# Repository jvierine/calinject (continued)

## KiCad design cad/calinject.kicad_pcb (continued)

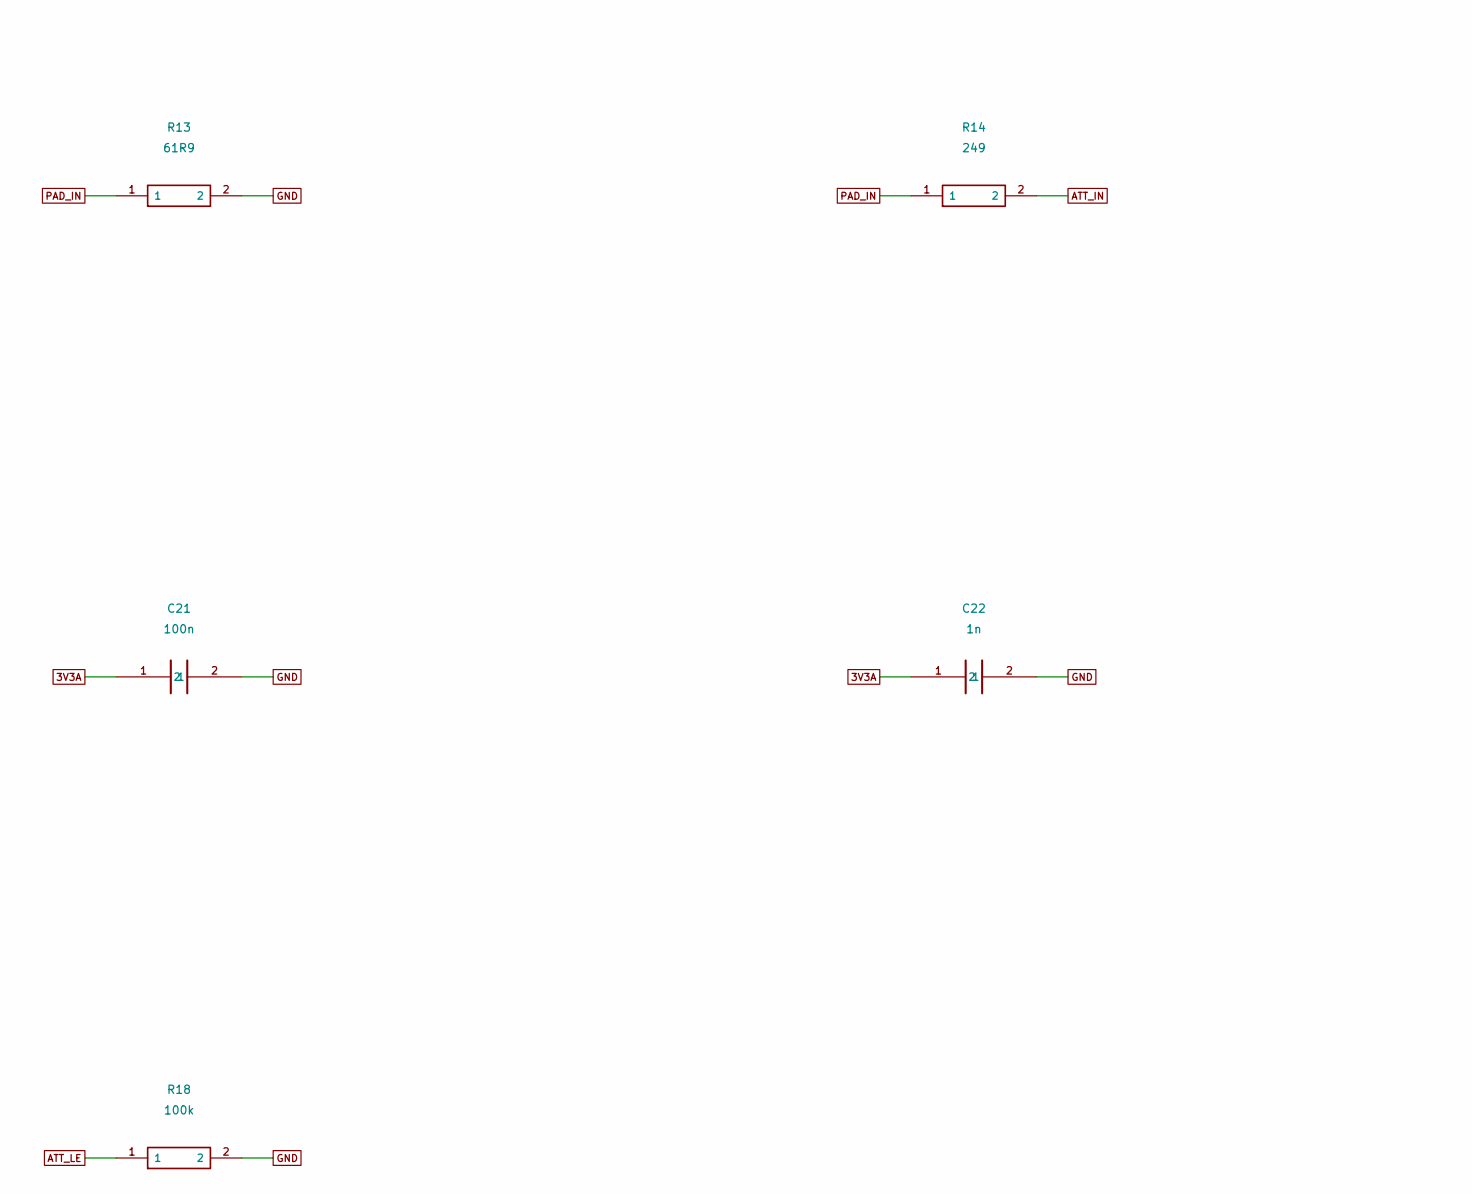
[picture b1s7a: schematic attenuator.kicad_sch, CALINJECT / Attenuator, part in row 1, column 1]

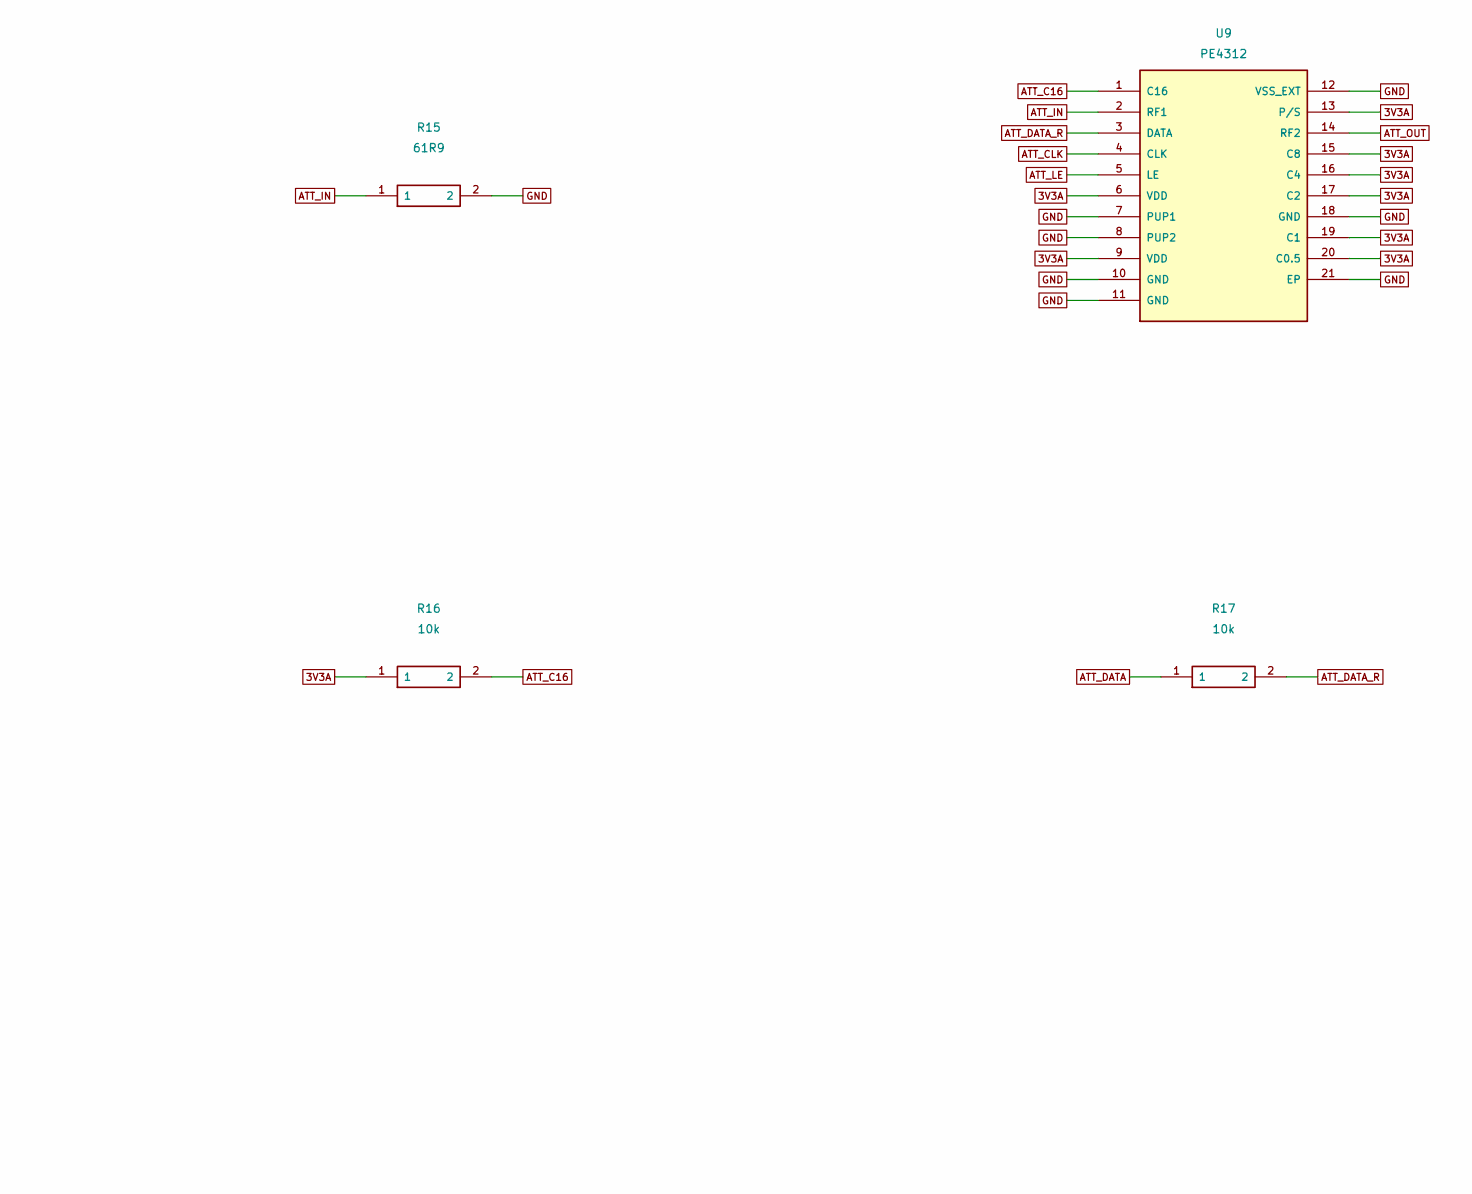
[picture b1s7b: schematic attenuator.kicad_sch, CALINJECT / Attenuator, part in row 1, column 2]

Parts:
C21: 100n; C_0603_C21
C22: 1n; C_0603_C22
R13: 61R9; R_0603_R13
R14: 249; R_0603_R14
R15: 61R9; R_0603_R15
R16: 10k; R_0603_R16
R17: 10k; R_0603_R17
R18: 100k; R_0603_R18
U9: PE4312; QFN20_4x4_EP_U9

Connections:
3V3A: C21.1, C22.1, R16.1, U9.6 (VDD), U9.9 (VDD), U9.13 (P/S), U9.15 (C8), U9.16 (C4), U9.17 (C2), U9.19 (C1), U9.20 (C0.5); also elsewhere on the board
ATT_C16: R16.2, U9.1 (C16)
ATT_CLK: U9.4 (CLK); also elsewhere on the board
ATT_DATA: R17.1; also elsewhere on the board
ATT_DATA_R: R17.2, U9.3 (DATA)
ATT_IN: R14.2, R15.1, U9.2 (RF1)
ATT_LE: R18.1, U9.5 (LE); also elsewhere on the board
ATT_OUT: U9.14 (RF2); also elsewhere on the board
GND: C21.2, C22.2, R13.2, R15.2, R18.2, U9.7 (PUP1), U9.8 (PUP2), U9.10 (GND), U9.11 (GND), U9.12 (VSS_EXT), U9.18 (GND), U9.21 (EP); also elsewhere on the board
PAD_IN: R13.1, R14.1; also elsewhere on the board

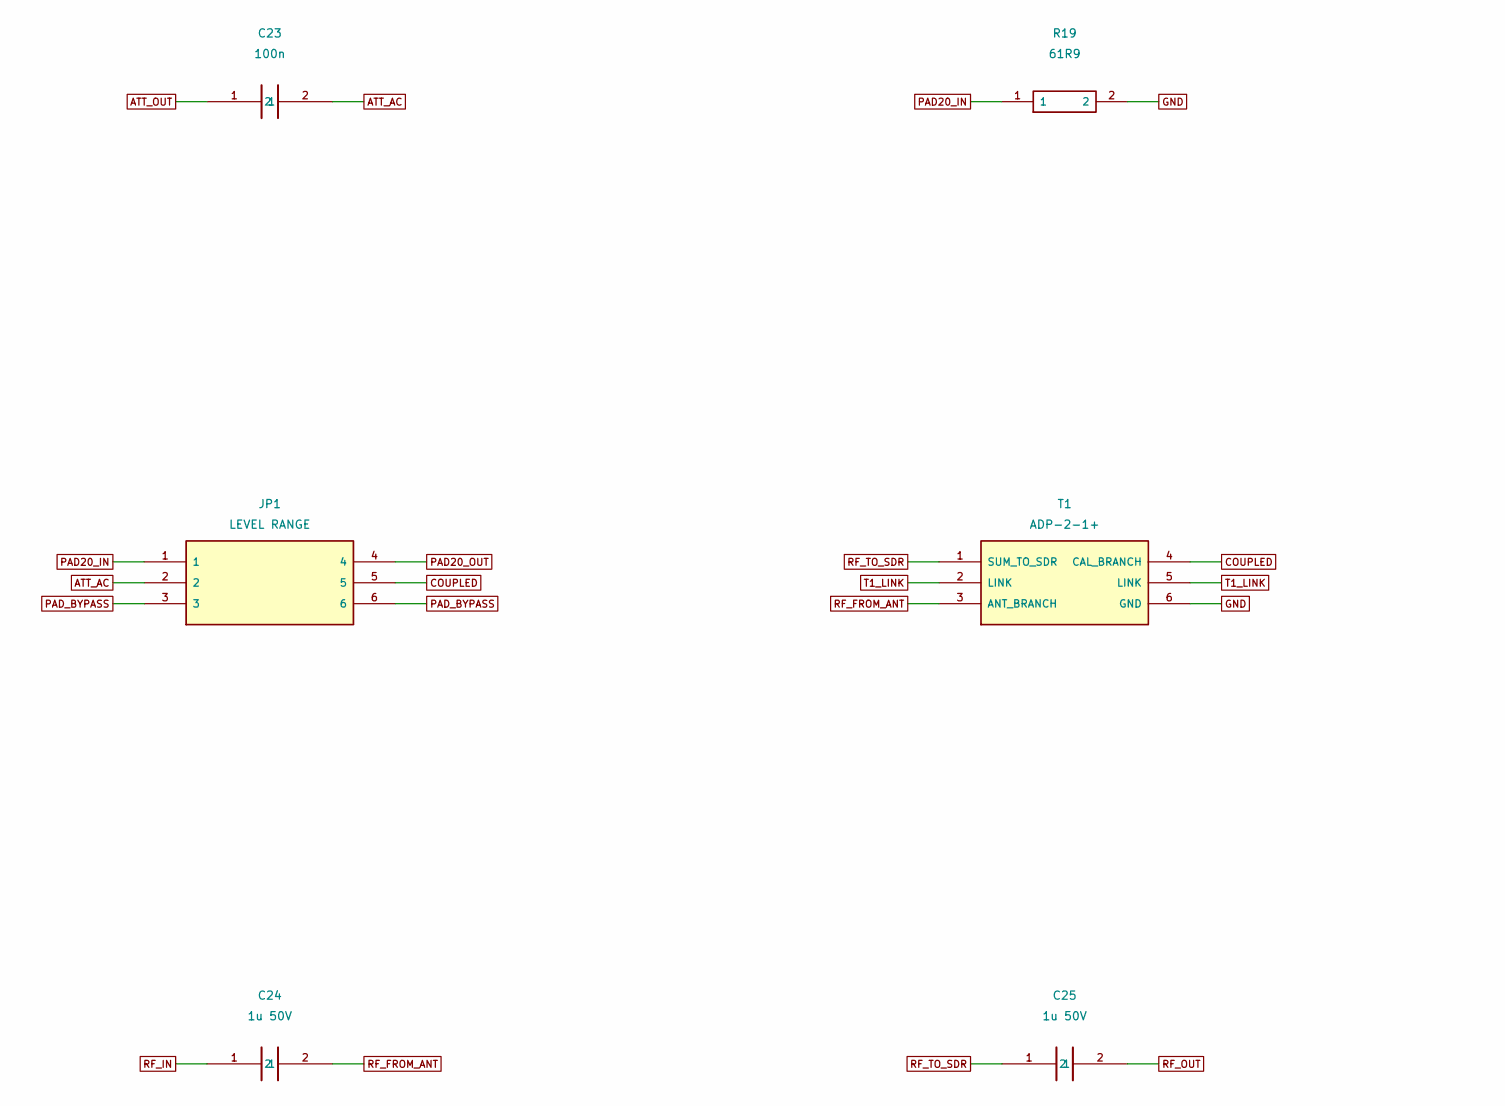
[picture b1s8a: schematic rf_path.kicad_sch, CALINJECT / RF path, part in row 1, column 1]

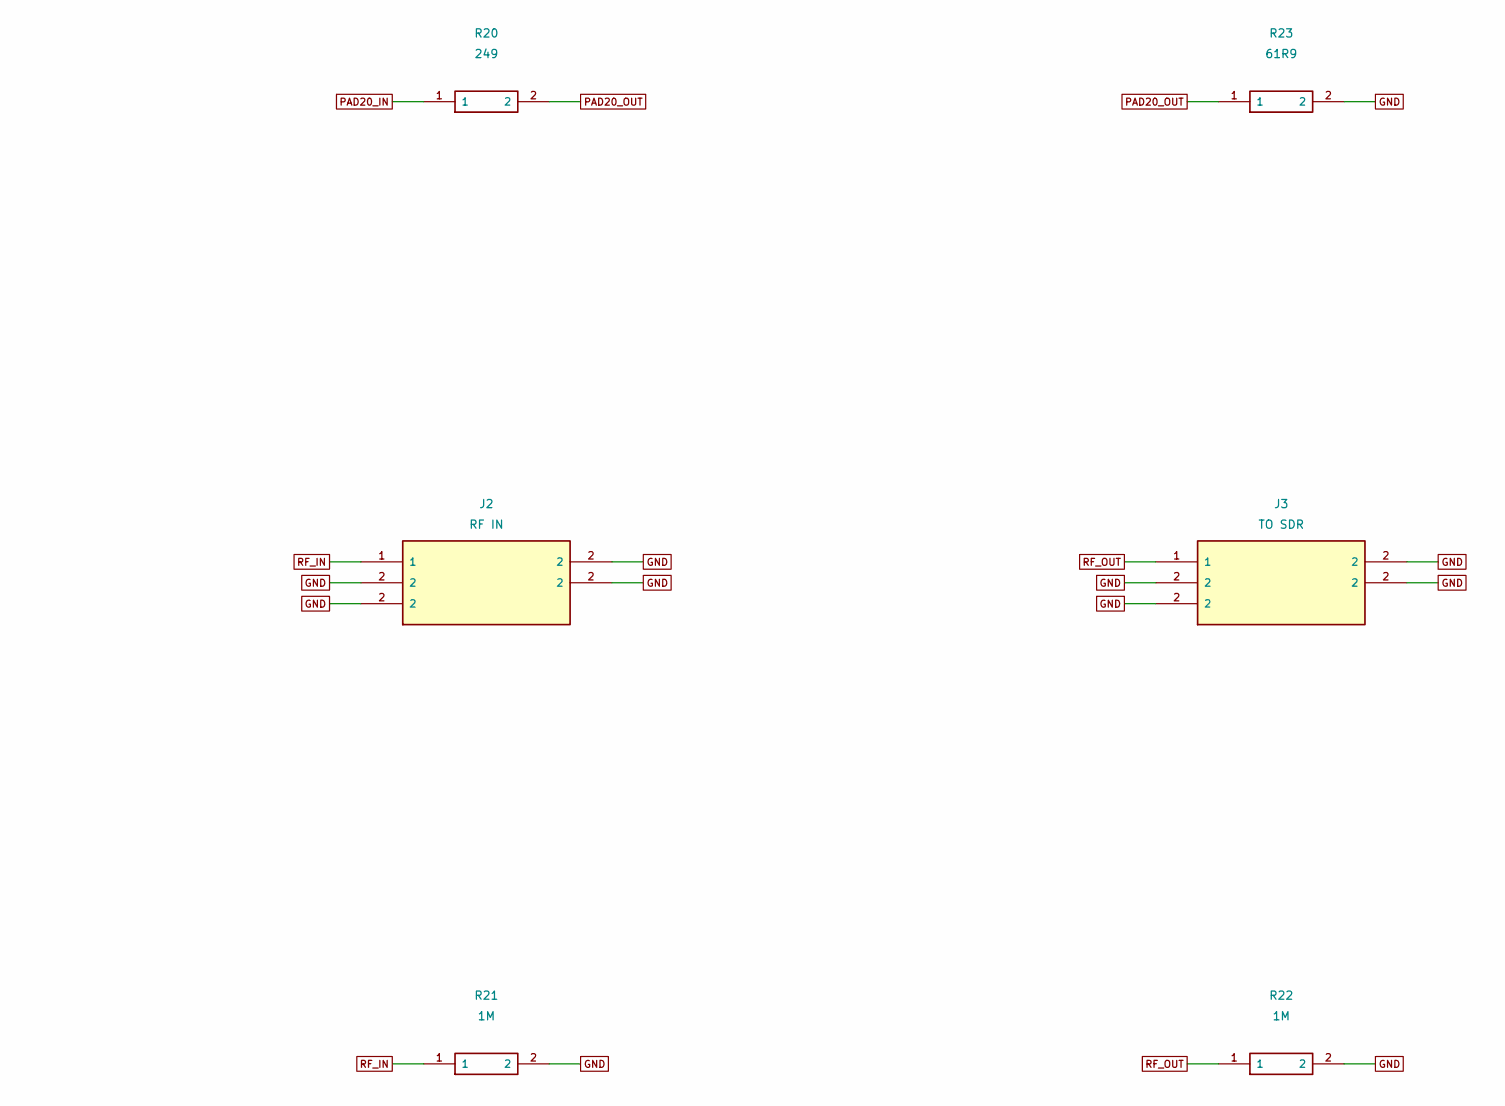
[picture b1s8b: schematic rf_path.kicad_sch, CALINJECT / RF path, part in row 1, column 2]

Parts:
C23: 100n; C_0603_C23
C24: 1u 50V; C_0805_C24
C25: 1u 50V; C_0805_C25
J2: RF IN; SMA_KWE_RA_J2
J3: TO SDR; SMA_KWE_RA_J3
JP1: LEVEL RANGE; Range_2x3_JP1
R19: 61R9; R_0603_R19
R20: 249; R_0603_R20
R21: 1M; R_0603_R21
R22: 1M; R_0603_R22
R23: 61R9; R_0603_R23
T1: ADP-2-1+; MiniCircuits_CD636_T1

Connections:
ATT_AC: C23.2, JP1.2
ATT_OUT: C23.1; also elsewhere on the board
COUPLED: JP1.5, T1.4 (CAL_BRANCH)
GND: J2.2, J3.2, R19.2, R21.2, R22.2, R23.2, T1.6 (GND); also elsewhere on the board
PAD20_IN: JP1.1, R19.1, R20.1
PAD20_OUT: JP1.4, R20.2, R23.1
PAD_BYPASS: JP1.3, JP1.6
RF_FROM_ANT: C24.2, T1.3 (ANT_BRANCH)
RF_IN: C24.1, J2.1, R21.1
RF_OUT: C25.2, J3.1, R22.1
RF_TO_SDR: C25.1, T1.1 (SUM_TO_SDR)
T1_LINK: T1.2 (LINK), T1.5 (LINK)

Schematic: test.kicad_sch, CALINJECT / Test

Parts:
TP1: PPS; TestPoint_TP1
TP2: 10M; TestPoint_TP2
TP3: GATE; TestPoint_TP3
TP4: VC; TestPoint_TP4
TP5: GND; TestPoint_TP5
TP6: 3V3; TestPoint_TP6

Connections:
3V3A: TP6.1; also elsewhere on the board
BURST_GATE: TP3.1; also elsewhere on the board
GND: TP5.1; also elsewhere on the board
PPS: TP1.1; also elsewhere on the board
TCXO_COUNT: TP2.1; also elsewhere on the board
VCTRL: TP4.1; also elsewhere on the board

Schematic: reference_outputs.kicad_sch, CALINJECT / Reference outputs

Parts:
C27: 100n; C_0603_C27
C28: 100n; C_0603_C28
J4: 10 MHz OUT; SMA_KWE_RA_J4
J5: 1 PPS OUT; SMA_KWE_RA_J5
R24: 100; R_0603_R24
R25: 100; R_0603_R25
R26: 0; R_0603_R26
R27: 10k; R_0603_R27
R28: 100; R_0603_R28
R29: 100; R_0603_R29
R30: 0; R_0603_R30
R31: 10k; R_0603_R31
R32: 1M; R_0603_R32
R33: 1M; R_0603_R33
U10: SN74LVC2G125; SSOP8_DCT_U10
U11: SN74LVC2G125; SSOP8_DCT_U11

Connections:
3V3A: C27.1, C28.1, R27.2, R31.2, U10.8 (VCC), U11.8 (VCC); also elsewhere on the board
CLK10: U10.2 (1A), U10.5 (2A); also elsewhere on the board
GND: C27.2, C28.2, J4.2, J5.2, R32.2, R33.2, U10.4 (GND), U11.4 (GND); also elsewhere on the board
PPS: U11.2 (1A), U11.5 (2A); also elsewhere on the board
REF10_OE_N: R27.1, U10.1 (1OE_N), U10.7 (2OE_N); also elsewhere on the board
REF10_OUT: J4.1, R26.2, R32.1
REF10_SUM: R24.2, R25.2, R26.1
REFPPS_OE_N: R31.1, U11.1 (1OE_N), U11.7 (2OE_N); also elsewhere on the board
REFPPS_OUT: J5.1, R30.2, R33.1
REFPPS_SUM: R28.2, R29.2, R30.1
U10_A: R24.1, U10.6 (1Y)
U10_B: R25.1, U10.3 (2Y)
U11_A: R28.1, U11.6 (1Y)
U11_B: R29.1, U11.3 (2Y)

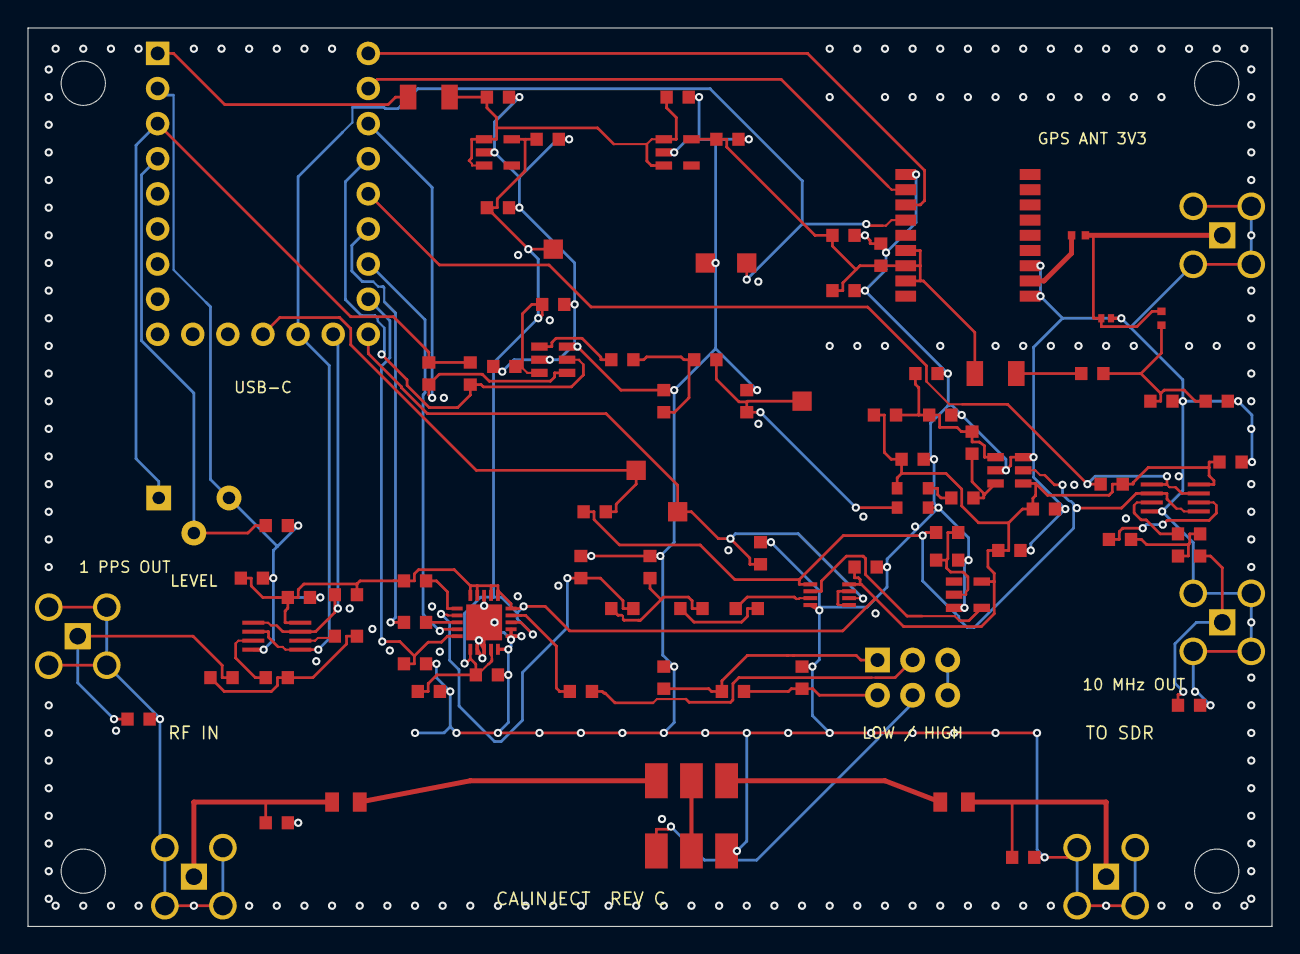
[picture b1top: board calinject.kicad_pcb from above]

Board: 4 copper layers, 90.0 x 65.0 mm, 99 parts (0 on the bottom side), 58 nets.

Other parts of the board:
H1: M3; Mount_M3_H1
H2: M3; Mount_M3_H2
H3: M3; Mount_M3_H3
H4: M3; Mount_M3_H4

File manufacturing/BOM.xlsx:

Designator | Comment | Footprint | Manufacturer | Manufacturer Part | Quantity | Assembly | LCSC Part #
U1 | RP2040-Zero | RP2040_Zero | Waveshare | RP2040-Zero | 1 | FACTORY MODULE | C5350143
U2,U3 | AP2112K-3.3 | SOT23_5 | Diodes Incorporated | AP2112K-3.3TRG1 | 2 | SMT
F1 | 500mA | F_1206 | Littelfuse | 1206L050/15YR | 1 | SMT
C1,C2,C3,C4,C6,C11,C12 | 4u7 | C_0603 | Murata | GRM188R61A475KE15D | 7 | SMT
U4 | MAX-M10S | MAX_M10S | u-blox | MAX-M10S-00B | 1 | SMT | C4153167
C5,C8,C10,C13,C15,C16,C18,C19,C21,C26,C27,C28,C29,C31,C32,C33 | 100n | C_0603 | Murata | GRM188R71C104KA01D | 16 | SMT
J1 | GPS ANT | SMA_KWE_RA | Lian Xin Technology | SMA-KWE | 1 | THT | C7498154
C7 | 100p | C_0402 | Murata | GRM1555C1H101JA01D | 1 | SMT
L1 | 27n | L_0402 | Murata | LQW15AN27NG80D | 1 | SMT
F2 | 50mA | F_1206 | Littelfuse | 1206L005/60WR | 1 | SMT
R1,R26,R30 | 0 | R_0603 | Yageo | RC0603FR-070RL | 3 | SMT
C9,C14,C22 | 1n | C_0603 | Murata | GRM1885C1H102JA01D | 3 | SMT
D1 | PESD5V0F1BL | DFN1006_2 | Nexperia | PESD5V0F1BL,315 | 1 | SMT | C45961
U5 | MCP4725A1 | SOT23_6 | Microchip | MCP4725A1T-E/CH | 1 | SMT | C61423
R2,R3 | 4k7 | R_0603 | Yageo | RC0603FR-074K7L | 2 | SMT
R4,R5 | 1k | R_0603 | Yageo | RC0603FR-071KL | 2 | SMT
Y1 | 10MHz VCTCXO | KDS_DSA321SDN | KDS Daishinku | 1XTV10000MDA | 1 | SMT | C253701
R6,R7,R8,R16,R17,R27,R31 | 10k | R_0603 | Yageo | RC0603FR-0710KL | 7 | SMT
U6 | TLV3501 | SOT23_6 | Texas Instruments | TLV3501AIDBVR | 1 | SMT
R9 | 330 | R_0603 | Yageo | RC0603FR-07330RL | 1 | SMT
R10 | 220 | R_0603 | Yageo | RC0603FR-07220RL | 1 | SMT
C17 | 22p | C_0603 | Samsung Electro-Mechanics | CL10C220JB8NNNC | 1 | SMT | C1653
U7 | SN74LVC1G14 | SOT23_5 | Texas Instruments | SN74LVC1G14DBVR | 1 | SMT
U8 | 74LVC2G08 | VSSOP8_DCU | Nexperia | 74LVC2G08DC,125 | 1 | SMT | C456135
R11,R18 | 100k | R_0603 | Yageo | RC0603FR-07100KL | 2 | SMT
R12 | 49R9 | R_0603 | Yageo | RC0603FR-0749R9L | 1 | SMT
C20,C23 | 100n | C_0603 | Murata | GRM188R71H104KA93D | 2 | SMT
R13,R15,R19,R23 | 61R9 | R_0603 | Yageo | RC0603FR-0761R9L | 4 | SMT
R14,R20 | 249 | R_0603 | Yageo | RC0603FR-07249RL | 2 | SMT
U9 | PE4312 | QFN20_4x4_EP | pSemi | PE4312C-Z | 1 | SMT
JP1 | LEVEL RANGE | Range_2x3 | FG / BOOMELE | FG-PZ2.54-1-03P | 2 | THT
T1 | ADP-2-1+ | MiniCircuits_CD636 | Mini-Circuits | ADP-2-1+ | 1 | SMT | C2683460
J2 | RF IN | SMA_KWE_RA | Lian Xin Technology | SMA-KWE | 1 | THT | C7498154
J3 | TO SDR | SMA_KWE_RA | Lian Xin Technology | SMA-KWE | 1 | THT | C7498154
C24,C25 | 1u 50V | C_0805 | Murata | GRM21BR71H105KA12L | 2 | SMT
R21,R22,R32,R33 | 1M | R_0603 | Yageo | RC0603FR-071ML | 4 | SMT
RV1 | 10k LEVEL | Bourns_3362P | Bourns | 3362P-1-103LF | 1 | THT
U10,U11 | SN74LVC2G125 | SSOP8_DCT | Texas Instruments | SN74LVC2G125DCTR | 2 | SMT | C206035
R24,R25,R28,R29 | 100 | R_0603 | Yageo | RC0603FR-07100RL | 4 | SMT
J4 | 10 MHz OUT | SMA_KWE_RA | Lian Xin Technology | SMA-KWE | 1 | THT | C7498154
J5 | 1 PPS OUT | SMA_KWE_RA | Lian Xin Technology | SMA-KWE | 1 | THT | C7498154

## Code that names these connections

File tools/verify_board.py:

"""Manufacturing consistency audit; run with KiCad bundled Python after exports."""
from pathlib import Path
import json,math,hashlib
import pcbnew as k
ROOT=Path(__file__).resolve().parents[1];board=ROOT/'cad/calinject.kicad_pcb';b=k.LoadBoard(str(board))
d=json.loads((ROOT/'cad/design.json').read_text());expected={p['ref']:p for p in d['parts']};actual={f.GetReference():f for f in b.GetFootprints()}
errors=[]
if set(expected)!=set(actual):errors.append('Footprint references differ from manifest')
for ref,p in expected.items():
 f=actual[ref]
 if abs(k.ToMM(f.GetPosition().x)-p['x'])>1e-5 or abs(k.ToMM(f.GetPosition().y)-p['y'])>1e-5:errors.append(ref+' placement')
 if (f.GetOrientationDegrees()-p['rot'])%360>1e-5:errors.append(ref+' rotation')
 if f.GetValue()!=p['value']:errors.append(ref+' value')
 expected_pads=[]
 for q in p['pads']:
  angle=math.radians(p['rot']);x=p['x']+q['x']*math.cos(angle)+q['y']*math.sin(angle);y=p['y']-q['x']*math.sin(angle)+q['y']*math.cos(angle)
  expected_pads.append((q['n'],round(x,4),round(y,4),round(q['w'],4),round(q['h'],4),round(q['drill'] or 0,4)))
 actual_pads=[(a.GetNumber(),round(k.ToMM(a.GetPosition().x),4),round(k.ToMM(a.GetPosition().y),4),round(k.ToMM(a.GetSize().x),4),round(k.ToMM(a.GetSize().y),4),round(k.ToMM(a.GetDrillSize().x),4)) for a in f.Pads()]
 if sorted(expected_pads)!=sorted(actual_pads):errors.append(ref+' pad geometry')
 for pad in f.Pads():
  q=next(q for q in p['pads'] if q['n']==pad.GetNumber())
  if q['kind']=='smd':
   layers={layer for layer in range(k.PCB_LAYER_ID_COUNT) if pad.IsOnLayer(layer)}
   allowed={k.F_Cu,k.F_Mask} if p['assembly']=='PCB' else {k.F_Cu,k.F_Mask,k.F_Paste}
   if layers!=allowed:errors.append(ref+'/'+q['n']+' layers')
  if q['net'] and pad.GetNetname()!=q['net']:errors.append(ref+'/'+q['n']+' net')
t1={p.GetNumber():p.GetNetname() for p in actual['T1'].Pads()}
if t1!={'1':'RF_TO_SDR','2':'T1_LINK','3':'RF_FROM_ANT','4':'COUPLED','5':'T1_LINK','6':'GND'}:errors.append('Combiner pin map')
tracks=list(b.GetTracks());vias=[v for v in tracks if isinstance(v,k.PCB_VIA)]
if any(v.GetViaType()!=k.VIATYPE_THROUGH for v in vias):errors.append('Non-through via')
if b.GetCopperLayerCount()!=4:errors.append('Copper layer count')
if min(k.ToMM(t.GetWidth()) for t in tracks if not isinstance(t,k.PCB_VIA))<.14999:errors.append('Track narrower than0.15mm')
cpl=json.loads((ROOT/'manufacturing/CPL.json').read_text());placed={row[0]:row for row in cpl[1:]};smd={p['ref']:p for p in d['parts'] if p['assembly']=='SMT'}
if set(placed)!=set(smd):errors.append('CPL component set')
for ref,p in smd.items():
 row=placed[ref]
 if abs(row[1]-p['x'])>1e-5 or abs(row[2]+p['y'])>1e-5 or row[4]!=p['rot']:errors.append(ref+' CPL placement')
for name in ['drc','erc']:
 report=json.loads((ROOT/('validation/'+name+'.json')).read_text())
 findings=sum(len(s['violations']) for s in report['sheets']) if name=='erc' else sum(len(report[x]) for x in ['violations','unconnected_items','schematic_parity'])
 if findings:errors.append(name+' findings')
result=dict(revision='C',board_sha256=hashlib.sha256(board.read_bytes()).hexdigest(),components=len(actual),smt_placements=len(placed),through_vias=len(vias),
 checks=['manifest placement/value/net consistency','SMT pad copper/mask/paste layers','testpoint no-paste layers','ADP-2-1+ pin map','four-layer/all-through-via rules','minimum track width','CPL consistency','zero ERC/DRC/connectivity/parity findings'],errors=errors)
(ROOT/'validation/manufacturing-checks.json').write_text(json.dumps(result,indent=2)+'\n')
print(json.dumps(result,indent=2));assert not errors,errors
